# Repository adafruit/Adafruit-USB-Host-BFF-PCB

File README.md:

## Adafruit USB Host BFF for QT Py or Xiao with MAX3421E PCB

<a href="http://www.adafruit.com/products/5956"><br/>
Click here to purchase one from the Adafruit shop</a>

PCB files for the Adafruit USB Host BFF for QT Py or Xiao with MAX3421E. 

Format is EagleCAD schematic and board layout
* https://www.adafruit.com/product/5956

### Description

Is your QT Py all alone, lacking a friend to travel the wide world with? When you were a kid, you may have learned about the "buddy" system. Well, this product is kind of like that! It is a board that will watch your QT Py's back and add a USB Host port.

That means that your tiny microcontroller project can have a keyboard, mouse, or disk drive plugged into it, opening up a huge ecosystem of common off-the-shelf devices that you can now integrate. The Adafruit USB Host BFF makes it easy to add USB Host support, especially now that TinyUSB supports it in the Arduino library as a 'native' interface for host support. 

This BFF uses the MAX3421E - a tried and true USB Host chip. It uses SPI plus an IRQ pin to send data to just about any USB device. Note that because the chip is older and you're limited to the SPI port speed, you won't get blazing 480Mbps high-speed data transfer. But for basic HID interfacing or even reading/writing to a Mass Storage device, it does work quite well. There's a famous USB Host Library that can be used, and its specialty is AVR support, but it also seems to support nRF52 and ESP32.

We personally recommend using the TinyUSB Arduino library - however, the trade-off is that the chip must have TinyUSB support already, which means it's great for RP2040, ESP32-S2 or S3, nRF52840, SAMD21/51 chips. Make sure your desired QT Py mainboard is supported between the two libraries before purchasing! 

To keep the BFF very compact, we use a micro-B USB "OTG" connector - a full sized USB Type A wouldn't fit! You'll need to use a basic OTG adapter (such as those sold for use with the Pi Zero) to convert to type A. Unlike our USB Host 'Wing we don't include a 5V power booster, so you will need to power the QT Py + BFF over USB or in some other way provide 5V on the 5V power line. However, to make it easier to power-cycle the peripheral, we have wired up a P-FET for switching the 5V host power on and off, you can either short the pin to A0 or you can use the MAX3421E's GPIO pin.

We include some header that you can solder to your QT Py. You can also pick up an Itsy Bitsy short female header kit to make it removable but compact; you'll need to trim the headers to 7 pins long.

Remember, you need driver support for the MAX3421E (see above for chips that are known to work). Unless you're using a generic mouse, keyboard, CDC serial, or USB mass storage device, you will also need a USB driver that knows how to talk to the device—and writing a driver is non-trivial.

QT Py or Xiao is not included!

### License

Adafruit invests time and resources providing this open source design, please support Adafruit and open-source hardware by purchasing products from [Adafruit](https://www.adafruit.com)!

Designed by Limor Fried/Ladyada for Adafruit Industries.

Creative Commons Attribution/Share-Alike, all text above must be included in any redistribution. 
See license.txt for additional details.

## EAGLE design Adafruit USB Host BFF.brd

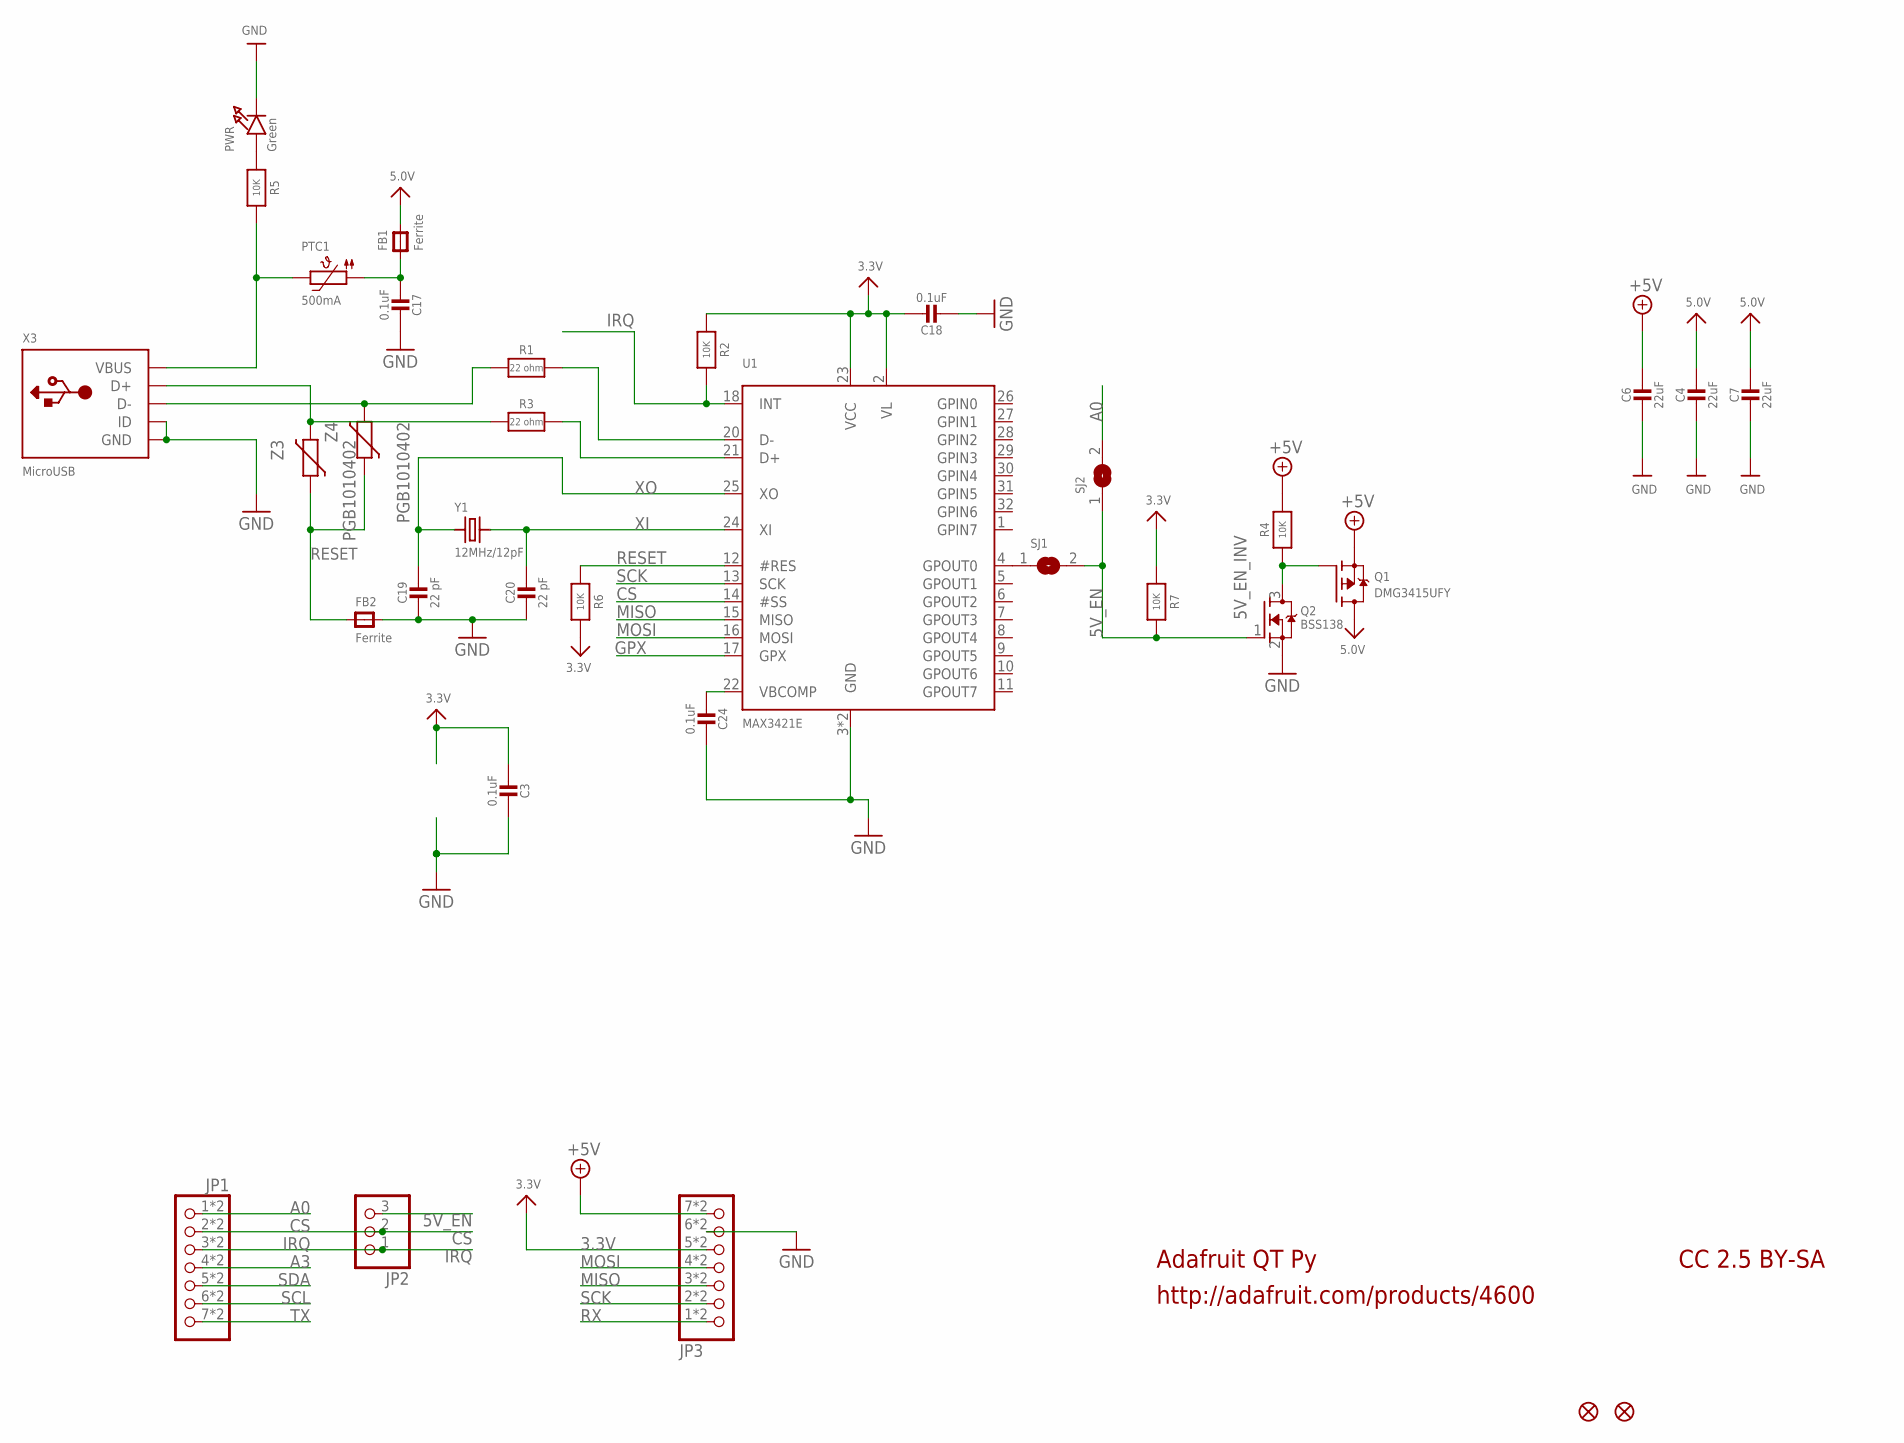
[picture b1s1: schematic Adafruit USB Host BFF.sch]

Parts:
C3, C17, C18, C24: 0.1uF; _0402NO
C4, C6, C7: 22uF; 0805-NO
C19, C20: 22 pF; _0402NO
FB1, FB2: Ferrite; 0603-NO
JP1, JP3: HEADER-1X7_CASTEL; 1X07_CASTEL
JP2: HEADER-1X3ROUND; 1X03_ROUND
PTC1: 500mA; 0805-NO
PWR: Green; CHIPLED_0603_NOOUTLINE
Q1: DMG3415UFY; DFN2015-3
Q2: BSS138; SC70
R1, R3: 22 ohm; _0402NO
R2, R4, R5, R6, R7: 10K; _0402NO
SJ1, SJ2: SOLDERJUMPER; SOLDERJUMPER_ARROW_NOPASTE
U1: MAX3421E; PQFP32_5X5MM
U$6, U$8: FIDUCIAL_0.5MM
X3: MicroUSB; SHOU_MICROXNJ073
Y1: 12MHz/12pF; CRYSTAL_2.5X2
Z3, Z4: PGB1010402; CT/CN0402

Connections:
3.3V: C3.1, C18.1, JP3.5, JP3.5C (5), R2.1, R6.2, R7.1, U1.2 (VL), U1.23 (VCC)
5.0V: C4.1, C7.1, FB1.2, Q1.3 (D)
5V_EN: JP2.3, Q2.1 (G), R7.2, SJ1.2, SJ2.1
5V_EN_INV: Q1.1 (G), Q2.3 (D), R4.1
+5V: C6.1, JP3.7, JP3.7C (7), Q1.2 (S), R4.2
A0: JP1.1, JP1.1C (1), SJ2.2
A3: JP1.4, JP1.4C (4)
CS: JP1.2, JP1.2C (2), JP2.2, U1.14 (#SS)
GND: C3.2, C4.2, C6.2, C7.2, C17.2, C18.2, C19.1, C20.1, C24.2, FB2.2, JP3.6, JP3.6C (6), PWR.C, Q2.2 (S), U1.3 (GND), U1.19 (GND), X3.BASE@1 (GND), X3.BASE@2 (GND), X3.GND, X3.ID, X3.SPRT@1 (GND), X3.SPRT@2 (GND), X3.SPRT@3 (GND), X3.SPRT@4 (GND)
GPX: U1.17 (GPX)
IRQ: JP1.3, JP1.3C (3), JP2.1, R2.2, U1.18 (INT)
MISO: JP3.3, JP3.3C (3), U1.15 (MISO)
MOSI: JP3.4, JP3.4C (4), U1.16 (MOSI)
unnamed: C24.1, U1.22 (VBCOMP)
unnamed: SJ1.1, U1.4 (GPOUT0)
unnamed: FB2.1, Z3.1, Z4.1
unnamed: PWR.A, R5.1
unnamed: R1.1, X3.D-, Z4.2
unnamed: R3.1, X3.D+, Z3.2
unnamed: R1.2, U1.20 (D-)
unnamed: R3.2, U1.21 (D+)
unnamed: PTC1.2, R5.2, X3.VBUS
unnamed: C17.1, FB1.1, PTC1.1
RESET: R6.1, U1.12 (#RES)
RX: JP3.1, JP3.1C (1)
SCK: JP3.2, JP3.2C (2), U1.13 (SCK)
SCL: JP1.6, JP1.6C (6)
SDA: JP1.5, JP1.5C (5)
TX: JP1.7, JP1.7C (7)
XI: C20.2, U1.24 (XI), Y1.3 (2)
XO: C19.2, U1.25 (XO), Y1.1

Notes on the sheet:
Adafruit QT Py
http://adafruit.com/products/4600
CC 2.5 BY-SA

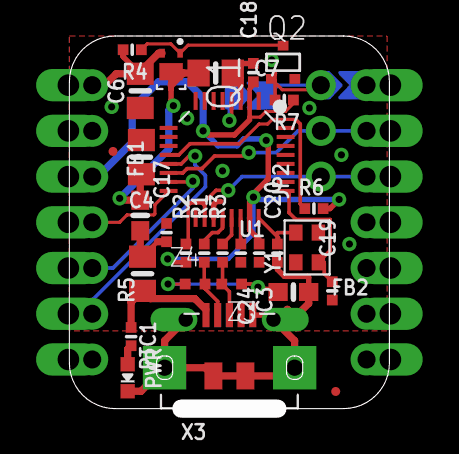
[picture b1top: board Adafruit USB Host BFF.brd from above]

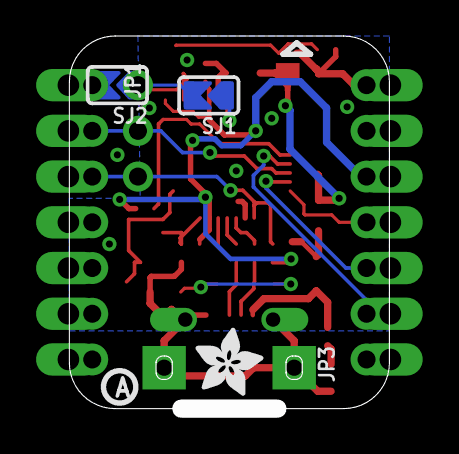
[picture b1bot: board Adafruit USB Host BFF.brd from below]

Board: 2 copper layers, 17.8 x 20.7 mm, 54 parts (11 on the bottom side), 30 nets.

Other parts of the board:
PLABEL0: PLABEL0
PLABEL1: PLABEL1
PLABEL2: PLABEL2
PLABEL3: PLABEL3
PLABEL4: PLABEL4
PLABEL5: PLABEL5
PLABEL6: PLABEL6
PLABEL7: PLABEL7
PLABEL8: PLABEL8
PLABEL9: PLABEL9
PLABEL10: PLABEL10
PLABEL11: PLABEL11
PLABEL12: PLABEL12
PLABEL13: PLABEL13
PLABEL14: PLABEL14
PLABEL15: PLABEL15
PLABEL16: PLABEL16
PLABEL17: PLABEL17
U$2: ADAFRUIT_3.5MM
U$13: PCBFEAT-REV-040

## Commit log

2024-04-30 cookiecutter

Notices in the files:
parts and their libraries:
microbuilder: This work is placed in the public domain, and may be freely used for commercial and non-commercial work with the following conditions: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
